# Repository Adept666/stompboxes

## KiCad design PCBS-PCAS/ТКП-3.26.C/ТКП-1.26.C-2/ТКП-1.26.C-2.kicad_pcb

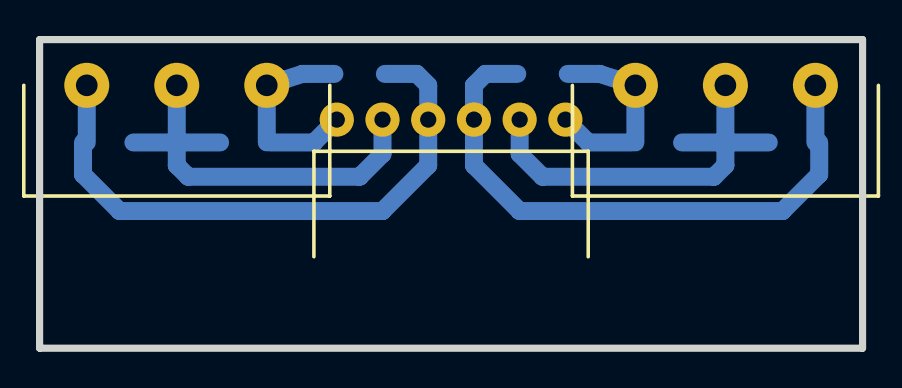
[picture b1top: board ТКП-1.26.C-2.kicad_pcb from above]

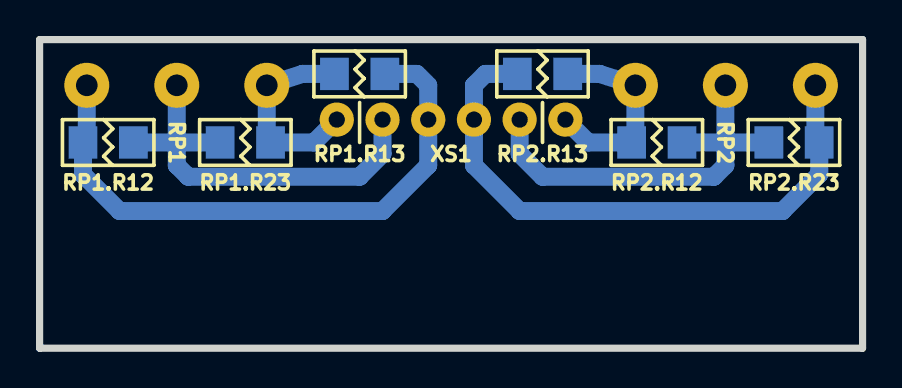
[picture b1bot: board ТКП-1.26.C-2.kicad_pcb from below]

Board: 2 copper layers, 45.7 x 17.1 mm, 9 parts (6 on the bottom side), 6 nets.

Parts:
RP1, RP2: B50K; RP-PDB181-K-20-P-CIRCULAR
RP1.R12, RP1.R13, RP1.R23, RP2.R12, RP2.R13, RP2.R23: X; R-SM-1206
XS1: PBS-06R; CON-PBS-06R-CIRCULAR

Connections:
unnamed: RP1.1, RP1.R12.2, RP1.R13.2, XS1.4
unnamed: RP1.2, RP1.R12.1, RP1.R23.2, XS1.5
unnamed: RP1.3, RP1.R13.1, RP1.R23.1, XS1.6
unnamed: RP2.1, RP2.R12.2, RP2.R13.2, XS1.1
unnamed: RP2.2, RP2.R12.1, RP2.R23.2, XS1.2
unnamed: RP2.3, RP2.R13.1, RP2.R23.1, XS1.3

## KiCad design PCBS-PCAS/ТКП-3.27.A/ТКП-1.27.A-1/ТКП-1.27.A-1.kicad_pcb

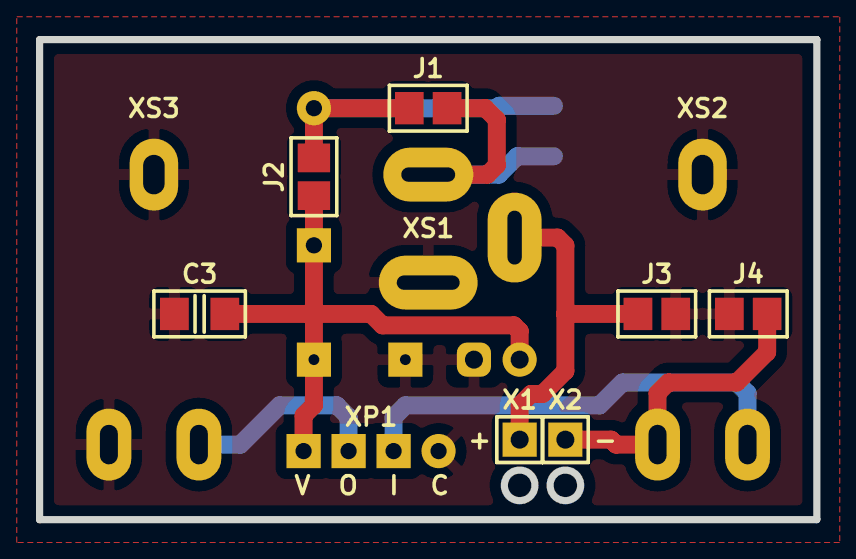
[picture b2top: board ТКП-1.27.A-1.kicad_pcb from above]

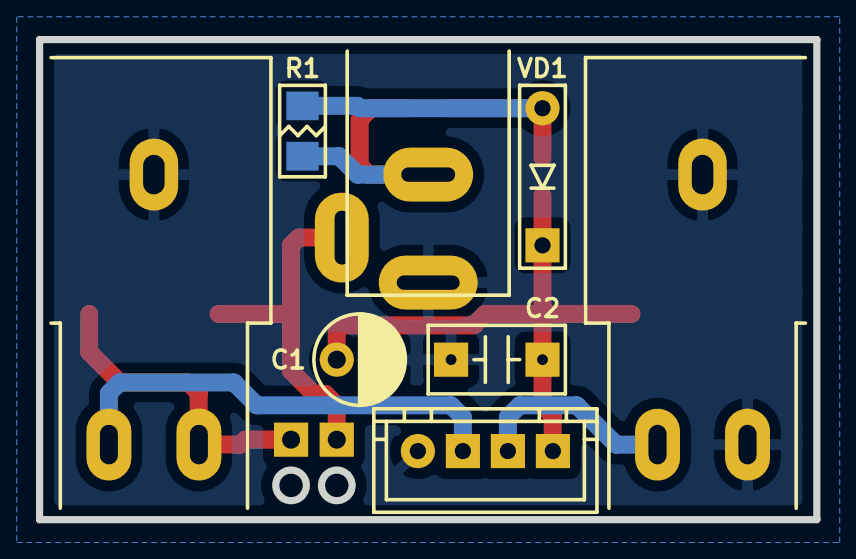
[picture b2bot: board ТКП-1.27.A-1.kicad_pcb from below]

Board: 2 copper layers, 43.2 x 26.7 mm, 16 parts (8 on the bottom side), 8 nets.

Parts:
C1: 107; CP-RADIAL-D05.0-P02.0-CLS
C2: 104; C-DISK-D04.2-T03.0-P05.08-d0.5
C3: 104; C-SM-1206
GB1: X; B-PP3-HV
J1: J1; J-SB-1206-2
J2: J2; J-SB-1206-2
J3: J3; J-SB-1206-2
J4: J4; J-SB-1206-2
R1: X; R-SM-1206
VD1: 5817; P-DO-41
X1, X2: X; CON-PAD-S-1.0-1.9
XP1: B4B-XH-A; CON-XH-B4B-A
XS1: DC-005; CON-DC-005-9V-OVAL
XS2: PJ-651A-01; CON-PJ-651A-01-IN-OVAL
XS3: PJ-651A-01; CON-PJ-651A-01-OUT-OVAL

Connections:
/IN-CON: XP1.2, XS2.T
/OUT-CON: XP1.3, XS3.T
/PP3-NEG: J4.1, X2.1, XS2.R
/PP3-POS: J3.1, X1.1, XS1.SN
COM: C1.-, C2.2, C3.2, J3.2, J4.2, XP1.1, XS1.C, XS2.S, XS3.R, XS3.S
unnamed: J1.1, R1.1, XS1.S
unnamed: J1.2, J2.1, R1.2, VD1.A
V: C1.+, C2.1, C3.1, J2.2, VD1.C, XP1.4

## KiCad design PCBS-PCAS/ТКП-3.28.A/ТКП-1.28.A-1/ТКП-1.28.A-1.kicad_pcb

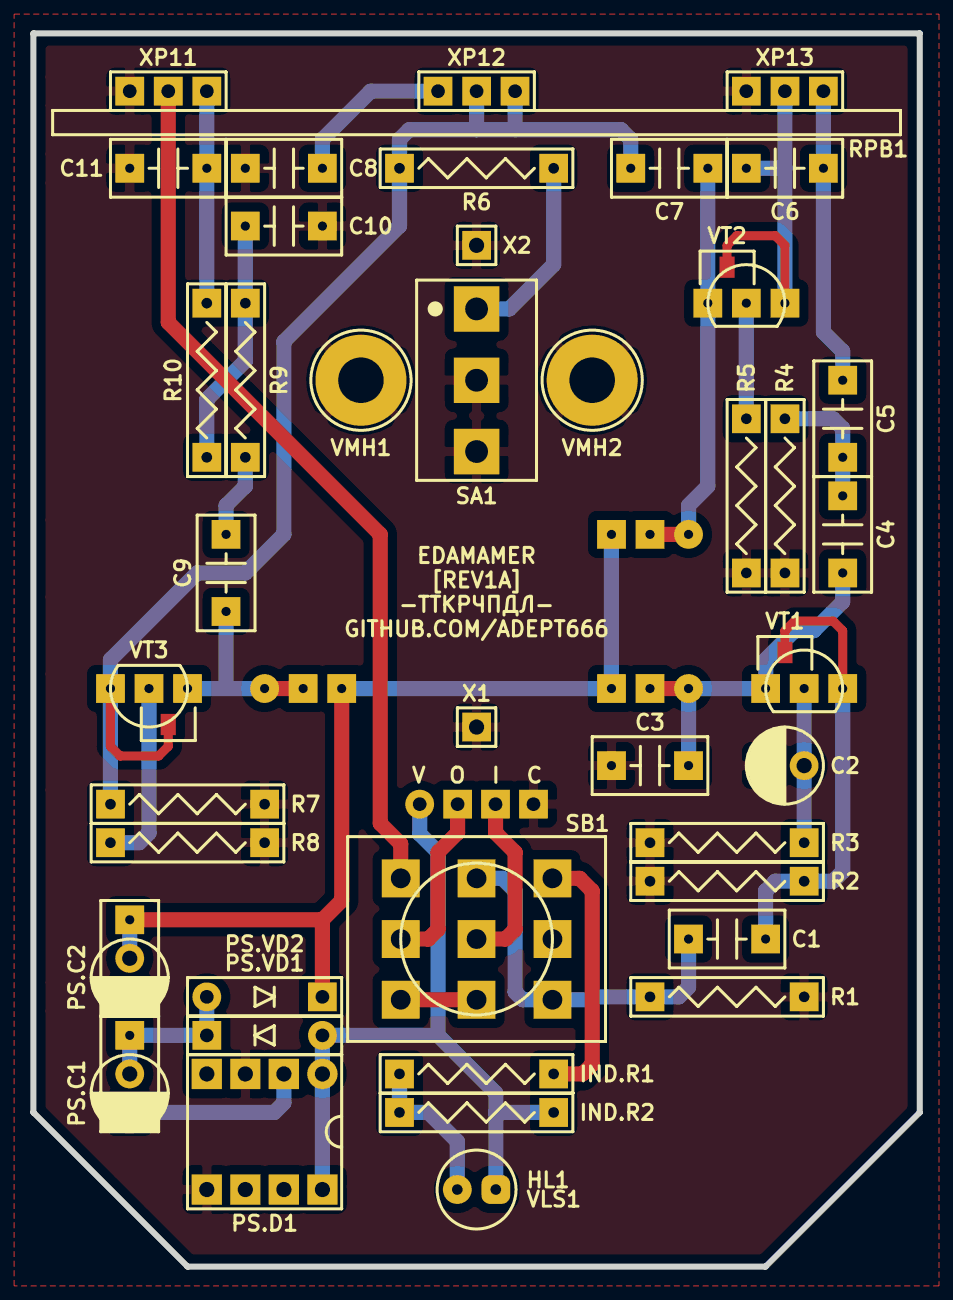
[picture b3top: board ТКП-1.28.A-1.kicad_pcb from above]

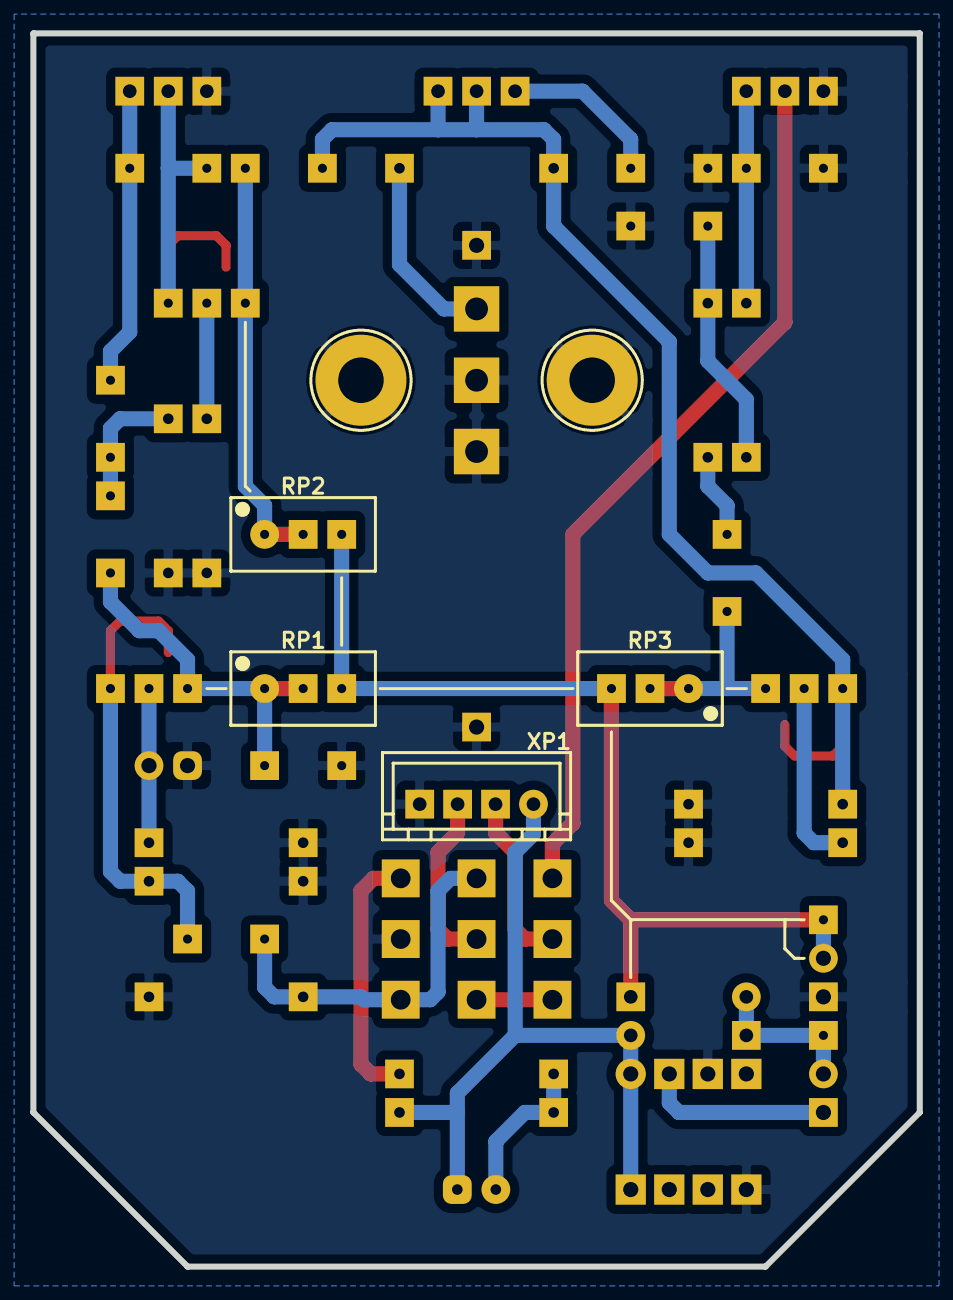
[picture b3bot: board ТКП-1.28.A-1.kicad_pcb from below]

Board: 2 copper layers, 58.4 x 81.3 mm, 46 parts (4 on the bottom side), 28 nets.

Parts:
C1: 223; C-DISK-D04.2-T03.0-P05.08-d0.5
C2: 336; CP-RADIAL-D05.0-P02.0-CLS
C3, C6: 471; C-DISK-D04.2-T03.0-P05.08-d0.5
C4, C5, C8: 472; C-DISK-D04.2-T03.0-P05.08-d0.5
C7, C9: 103; C-DISK-D04.2-T03.0-P05.08-d0.5
C10, C11: 332; C-DISK-D04.2-T03.0-P05.08-d0.5
HL1: FYL-5013URC; LED-ROUND-05.0-UNI-SH-SPACER-PNL-5.3
IND.R1: 472; R-MFR-25
IND.R2: X; R-MFR-25
PS.C1, PS.C2: 105; C-DISK-D04.2-T03.0-P05.08-d0.5-OR-CP-RADIAL-D05.0-P02.0-CLS
PS.D1: 7660S; P-DIP-08
PS.VD1, PS.VD2: 400x; P-DO-41
R1, R2: 105; R-MFR-25
R3: 152; R-MFR-25
R4, R7: 474; R-MFR-25
R5: 272; R-MFR-25
R6: 124; R-MFR-25
R8: 221; R-MFR-25
R9, R10: 123; R-MFR-25
RP1, RP2: 100K; RP-3296W
RP3: 50K; RP-3296W
RPB1: A100K-A500K-A500K; RPB-1590N1-18-3x17-1.6-PNL-7.4-2.8
SA1: MTS-102-A2; SW-MTS-102-A2-3.0-PNL-6.0
SB1: PBS-24-302SP; SW-PBS-24-302SP-2.5-PNL-13.0
VE1: 1590N1; 1590N1_A1
VLS1: BR-12.7; VLS-BR
VMH1, VMH2: DI5M3x18; VMH-STA-DA5-PNL-3.0
VT1, VT2: J201; P-SOT-23-D-S-G-OR-TO-92-D-S-G
VT3: 5457; P-SOT-23-D-S-G-OR-TO-92-D-S-G
X1, X2: COM; CON-PAD-S-1.0-1.9
XB1: 1590N1 Connector Board; XB-1590N1
XP1: B4B-XH-A; CON-XH-B4B-A

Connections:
/IN-CIR: C1.1, R1.2, SB1.NC3, SB1.NO2
/IN-CON: SB1.COM2, XP1.3
/LED: IND.R1.1, SB1.NO3
/OUT-CIR: RPB1.12, SB1.NO1
/OUT-CON: SB1.COM1, XP1.2
COM: C2.-, C3.2, C8.2, C10.2, C11.2, PS.C2.-, PS.D1.3, PS.D1.5, R1.1, R2.1, R3.1, R4.1, R5.1, R7.1, R8.1, RPB1.11, RPB1.31, SA1.COM, SA1.NO, SB1.COM3, VMH1.0, VMH2.0, X1.1, X2.1, XP1.4
unnamed: C1.2, R2.2, VT1.G
unnamed: C2.+, R3.2, VT1.S
unnamed: C3.1, C4.1, RP1.1, RP1.2, VT1.D
unnamed: C4.2, C5.1, R4.2
unnamed: C5.2, C6.1, RPB1.33
unnamed: C6.2, RPB1.32, VT2.G
unnamed: C7.1, RP2.1, RP2.2, VT2.D
unnamed: C7.2, R6.2, R7.2, RPB1.22, RPB1.23, VT3.G
unnamed: C8.1, RPB1.21
unnamed: C9.1, RP3.1, RP3.2, VT3.D
unnamed: C9.2, R9.1
unnamed: C10.1, R9.2, R10.1
unnamed: C11.1, R10.2, RPB1.13
unnamed: HL1.C, IND.R1.2, IND.R2.1
unnamed: PS.C1.+, PS.VD1.C, PS.VD2.A
unnamed: PS.C1.-, PS.D1.2
unnamed: R5.2, VT2.S
unnamed: R6.1, SA1.NC
unnamed: R8.2, VT3.S
unnamed: SB1.NC1, SB1.NC2
V: HL1.A, IND.R2.2, PS.D1.1, PS.D1.8, PS.VD1.A, XP1.1
VA: PS.C2.+, PS.VD2.C, RP1.3, RP2.3, RP3.3

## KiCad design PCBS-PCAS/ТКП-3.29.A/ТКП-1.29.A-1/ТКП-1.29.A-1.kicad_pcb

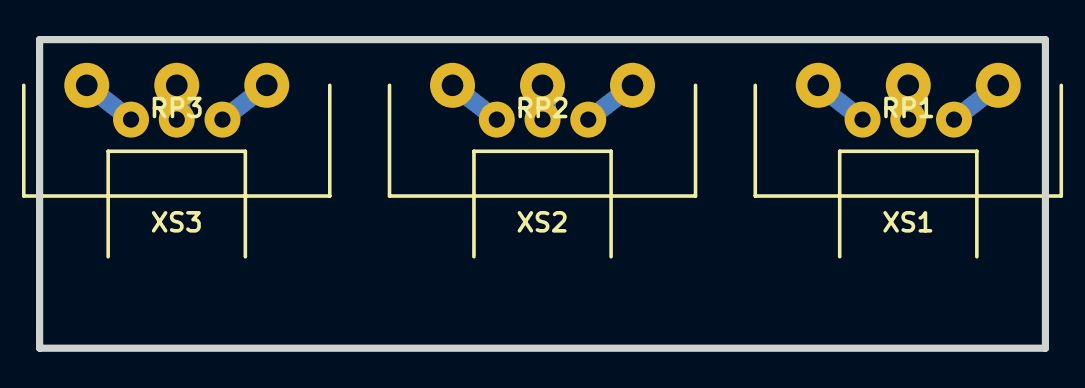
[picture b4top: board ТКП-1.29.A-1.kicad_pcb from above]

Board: 2 copper layers, 55.9 x 17.1 mm, 6 parts (0 on the bottom side), 9 nets.

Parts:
RP1: RP1: A100K; RP-PDB181-K-20-P-CIRCULAR
RP2: RP2: A500K; RP-PDB181-K-20-P-CIRCULAR
RP3: RP3: A500K; RP-PDB181-K-20-P-CIRCULAR
XS1, XS2, XS3: PBS-03R; CON-PBS-03R-CIRCULAR

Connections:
unnamed: RP1.1, XS1.3
unnamed: RP1.2, XS1.2
unnamed: RP1.3, XS1.1
unnamed: RP2.1, XS2.3
unnamed: RP2.2, XS2.2
unnamed: RP2.3, XS2.1
unnamed: RP3.1, XS3.3
unnamed: RP3.2, XS3.2
unnamed: RP3.3, XS3.1

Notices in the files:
PCBS-PCAS/ТКП-3.26.C/ТКП-1.26.C-2/ТКП-1.26.C-2.kicad_pcb:
This project is licensed under GNU General Public License v3.0 or later
